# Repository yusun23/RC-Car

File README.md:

# RC-Car
Schematics for the PCB, CAD files for the Chassis and Frame Design. Along with the Code for the Embedded Systems and the materials needed to accomplish this.

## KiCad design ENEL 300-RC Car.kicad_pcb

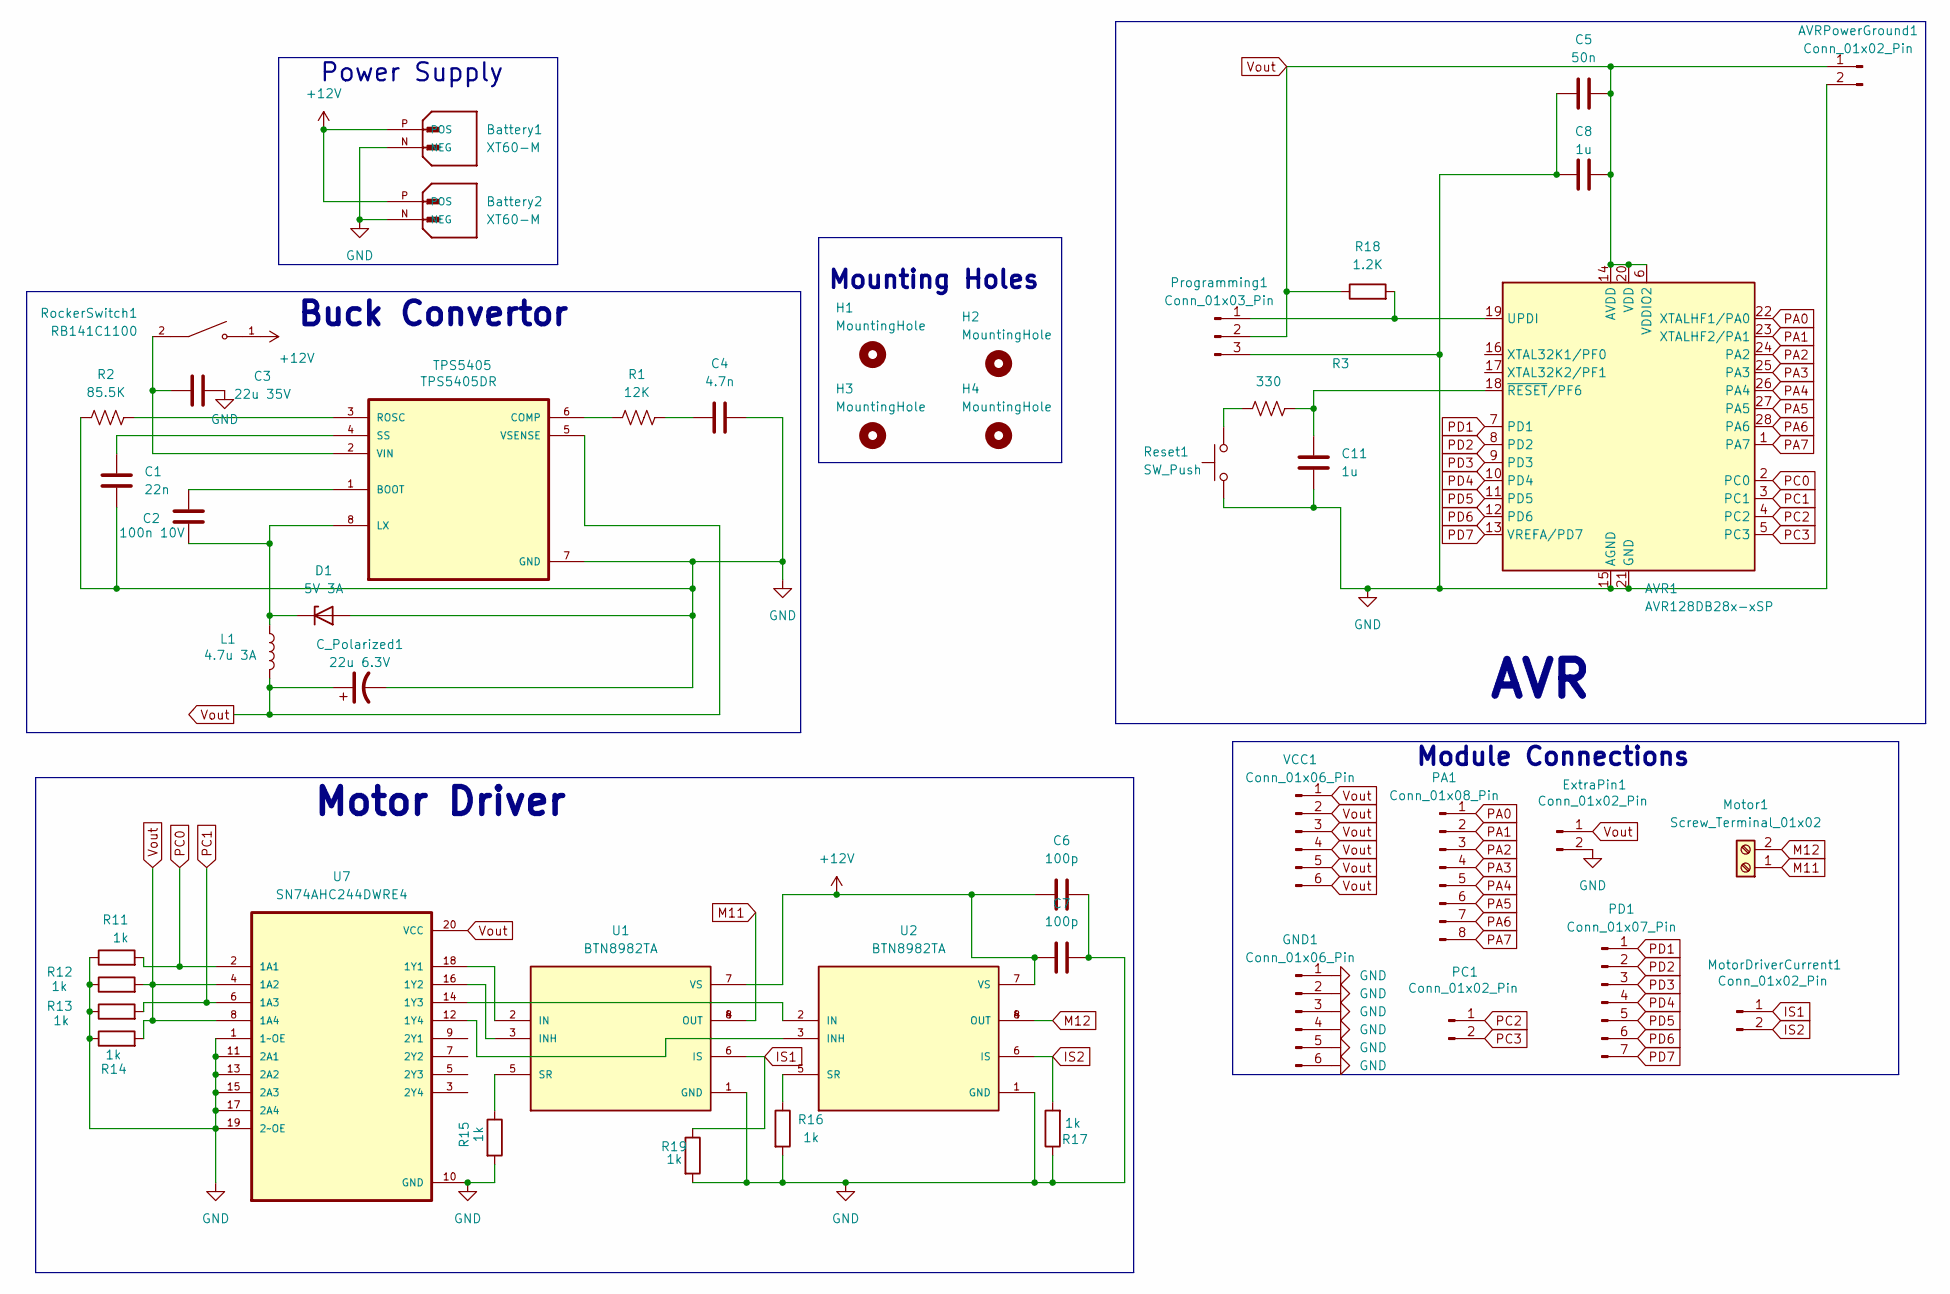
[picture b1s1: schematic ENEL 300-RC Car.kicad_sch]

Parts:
AVR1: AVR128DB28x-xSP; DIP-28_W7.62mm
AVRPowerGround1: Conn_01x02_Pin; PinHeader_1x02_P2.54mm_Vertical
Battery1, Battery2: XT60-M; AMASS_XT60-M; PARTREV V1.2
C1: 22n; C_Disc_D4.7mm_W2.5mm_P5.00mm
C2: 100n 10V; C_Radial_D4.0mm_H7.0mm_P1.50mm
C3: 22u 35V; C_Radial_D4.0mm_H7.0mm_P1.50mm
C4: 4.7n; C_Disc_D4.7mm_W2.5mm_P5.00mm
C5: 50n; C_Disc_D4.7mm_W2.5mm_P5.00mm
C6, C7: 100p; C_Disc_D4.7mm_W2.5mm_P5.00mm
C8, C11: 1u; C_Radial_D5.0mm_H11.0mm_P2.00mm
C_Polarized1: 22u 6.3V; CP_Radial_D5.0mm_P2.50mm
D1: 5V 3A; D_DO-41_SOD81_P7.62mm_Horizontal
ExtraPin1: Conn_01x02_Pin; PinHeader_1x02_P2.54mm_Vertical
GND1: Conn_01x06_Pin; PinHeader_1x06_P2.54mm_Vertical
H1, H2, H3, H4: MountingHole; MountingHole_3.2mm_M3
L1: 4.7u 3A; L_Radial_D7.0mm_P3.00mm
Motor1: Screw_Terminal_01x02; TerminalBlock_MetzConnect_Type701_RT11L02HGLU_1x02_P6.35mm_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
MotorDriverCurrent1: Conn_01x02_Pin; PinHeader_1x02_P2.54mm_Vertical
PA1: Conn_01x08_Pin; PinHeader_1x08_P2.54mm_Vertical
PC1: Conn_01x02_Pin; PinHeader_1x02_P2.54mm_Vertical
PD1: Conn_01x07_Pin; PinHeader_1x07_P2.54mm_Vertical
Programming1: Conn_01x03_Pin; PinHeader_1x03_P2.54mm_Vertical
R1: 12K; R_Axial_DIN0204_L3.6mm_D1.6mm_P5.08mm_Horizontal
R2: 85.5K; R_Axial_DIN0204_L3.6mm_D1.6mm_P5.08mm_Horizontal
R3: 330; R_Axial_DIN0204_L3.6mm_D1.6mm_P5.08mm_Horizontal
R11, R12, R13, R14, R15, R16, R17, R19: 1k; R_Axial_DIN0204_L3.6mm_D1.6mm_P5.08mm_Horizontal
R18: 1.2K; R_Axial_DIN0204_L3.6mm_D1.6mm_P5.08mm_Horizontal
Reset1: SW_Push; SW_PUSH_6mm
RockerSwitch1: RB141C1100; SW_RB141C1100; PARTREV C
TPS5405: TPS5405DR; SOIC127P599X175-8N
U1, U2: BTN8982TA; DPAK127P1500X440-8N; PARTREV 1.0
U7: SN74AHC244DWRE4; SOIC127P1030X265-20N
VCC1: Conn_01x06_Pin; PinHeader_1x06_P2.54mm_Vertical

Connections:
+12V: Battery1.P (POS), Battery2.P (POS), C6.1, C7.1, RockerSwitch1.1, U1.7 (VS), U2.7 (VS)
GND: AVR1.15 (AGND), AVR1.21 (GND), AVRPowerGround1.2, Battery1.N (NEG), Battery2.N (NEG), C1.2, C3.2, C4.2, C5.1, C6.2, C7.2, C8.1, C11.2, C_Polarized1.2, D1.2 (A), ExtraPin1.2, GND1.1, GND1.2, GND1.3, GND1.4, GND1.5, GND1.6, Programming1.3, R2.1, R11.1, R12.1, R13.1, R14.1, R15.2, R16.2, R17.1, R19.2, Reset1.1, TPS5405.7 (GND), U1.1 (GND), U2.1 (GND), U7.1 (1~OE), U7.10 (GND), U7.11 (2A1), U7.13 (2A2), U7.15 (2A3), U7.17 (2A4), U7.19 (2~OE)
IS1: MotorDriverCurrent1.1, R19.1, U1.6 (IS)
IS2: MotorDriverCurrent1.2, R17.2, U2.6 (IS)
M11: Motor1.1, U1.4 (OUT), U1.8 (OUT)
M12: Motor1.2, U2.4 (OUT), U2.8 (OUT)
unnamed: AVR1.19 (UPDI), Programming1.1, R18.2
unnamed: AVR1.18 (~RESET/PF6), C11.1, R3.2
unnamed: C4.1, R1.2
unnamed: C2.2, D1.1 (K), L1.1, TPS5405.8 (LX)
unnamed: R3.1, Reset1.2
unnamed: C2.1, TPS5405.1 (BOOT)
unnamed: R1.1, TPS5405.6 (COMP)
unnamed: R2.2, TPS5405.3 (ROSC)
unnamed: C1.1, TPS5405.4 (SS)
unnamed: C3.1, RockerSwitch1.2, TPS5405.2 (VIN)
unnamed: U1.2 (IN), U7.18 (1Y1)
unnamed: U1.3 (INH), U7.16 (1Y2)
unnamed: R15.1, U1.5 (SR)
unnamed: U2.2 (IN), U7.14 (1Y3)
unnamed: U2.3 (INH), U7.12 (1Y4)
unnamed: R16.1, U2.5 (SR)
PA0: AVR1.22 (XTALHF1/PA0), PA1.1
PA1: AVR1.23 (XTALHF2/PA1), PA1.2
PA2: AVR1.24 (PA2), PA1.3
PA3: AVR1.25 (PA3), PA1.4
PA4: AVR1.26 (PA4), PA1.5
PA5: AVR1.27 (PA5), PA1.6
PA6: AVR1.28 (PA6), PA1.7
PA7: AVR1.1 (PA7), PA1.8
PC0: AVR1.2 (PC0), R11.2, U7.2 (1A1)
PC1: AVR1.3 (PC1), R13.2, U7.6 (1A3)
PC2: AVR1.4 (PC2), PC1.1
PC3: AVR1.5 (PC3), PC1.2
PD1: AVR1.7 (PD1), PD1.1
PD2: AVR1.8 (PD2), PD1.2
PD3: AVR1.9 (PD3), PD1.3
PD4: AVR1.10 (PD4), PD1.4
PD5: AVR1.11 (PD5), PD1.5
PD6: AVR1.12 (PD6), PD1.6
PD7: AVR1.13 (VREFA/PD7), PD1.7
Vout: AVR1.6 (VDDIO2), AVR1.14 (AVDD), AVR1.20 (VDD), AVRPowerGround1.1, C5.2, C8.2, C_Polarized1.1, ExtraPin1.1, L1.2, Programming1.2, R12.2, R14.2, R18.1, TPS5405.5 (VSENSE), U7.4 (1A2), U7.8 (1A4), U7.20 (VCC), VCC1.1, VCC1.2, VCC1.3, VCC1.4, VCC1.5, VCC1.6

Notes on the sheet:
AVR
Mounting Holes
Motor Driver
Module Connections
Buck Convertor
Power Supply

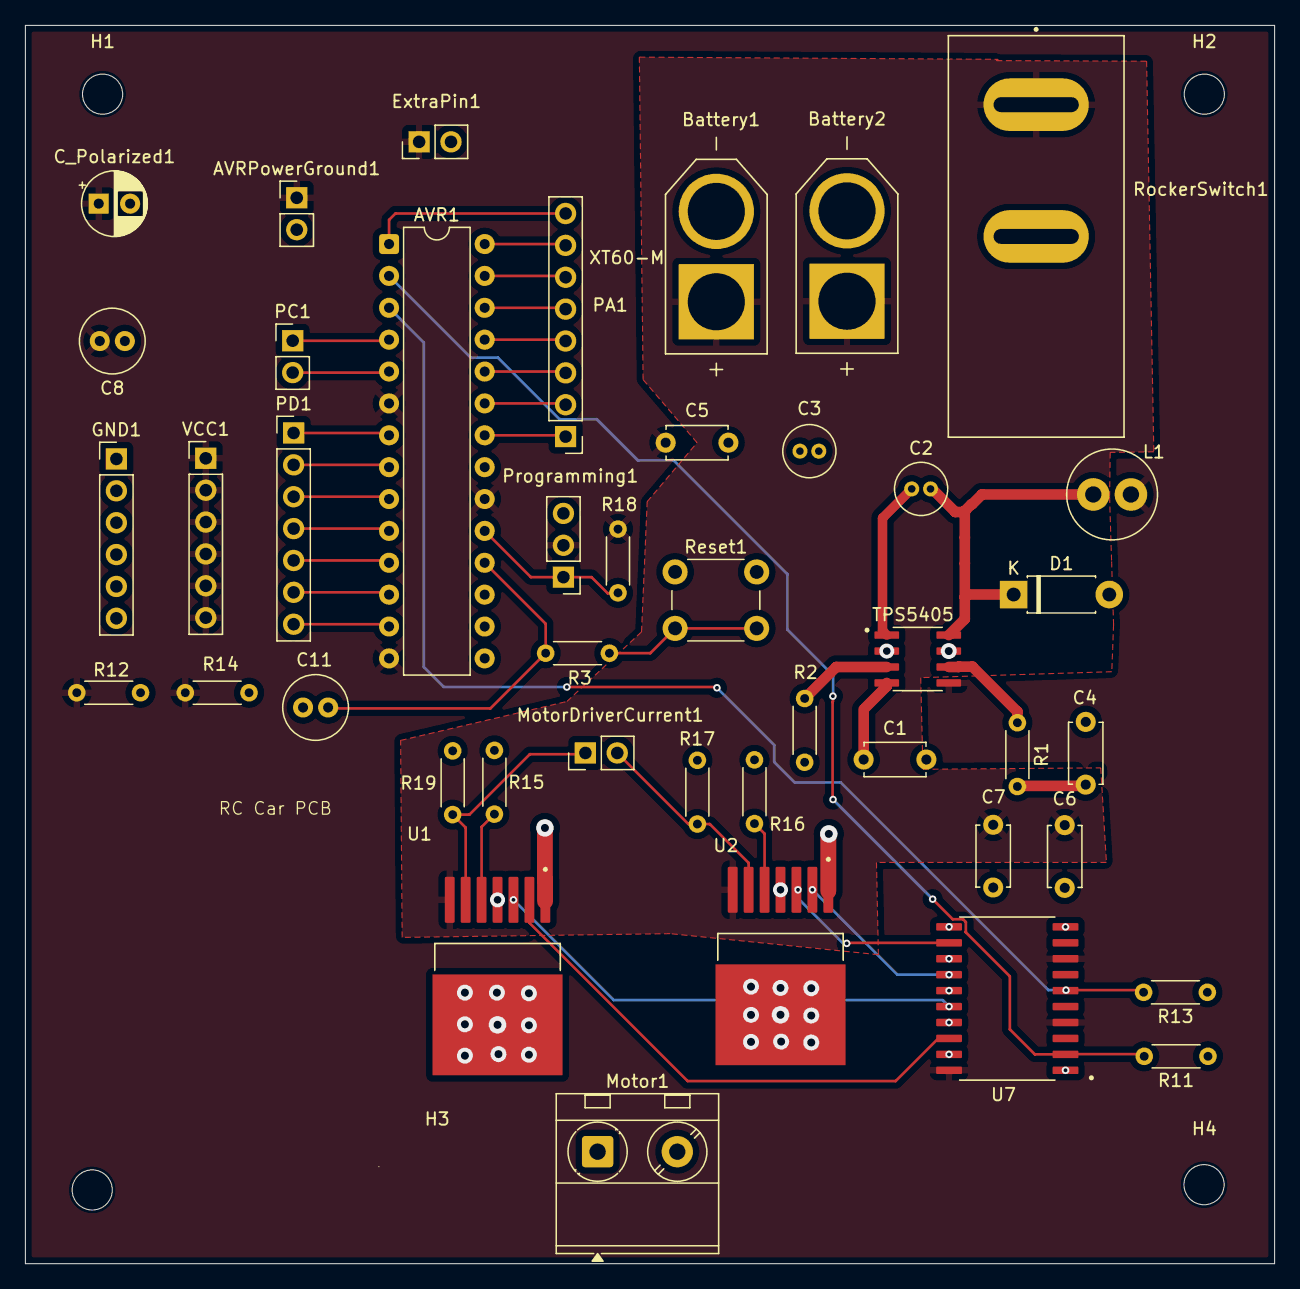
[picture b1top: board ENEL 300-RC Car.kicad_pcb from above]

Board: 2 copper layers, 99.5 x 98.7 mm, 47 parts (1 on the bottom side), 42 nets.

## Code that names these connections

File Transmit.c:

#include <avr/io.h>
#include <util/delay.h>

#define F_CPU 16000000UL

void USART0_Init(void) {
    USART0.BAUD = 6666;  // Approx. 9600 baud
    USART0.CTRLC = USART_CMODE_ASYNCHRONOUS_gc |
                   USART_PMODE_DISABLED_gc |
                   USART_CHSIZE_8BIT_gc;
    PORTA.DIRSET = PIN0_bm;  // TX
    PORTA.DIRCLR = PIN1_bm;  // RX
    USART0.CTRLB = USART_TXEN_bm | USART_RXEN_bm;
}

void USART0_Transmit(uint8_t data) {
    while (!(USART0.STATUS & USART_DREIF_bm));
    USART0.TXDATAL = data;
}

void init_io(void) {
    // Buttons on PA6, PA7
    PORTA.DIRCLR = 0b11000000;
    
    // Joystick on PD1 (Y) and PD2 (X)
    PORTD.DIRCLR = PIN1_bm | PIN2_bm;
}

void ADC0_Init(void) {
    VREF.ADC0REF = 0b10000101;      // VDD reference
    ADC0.CTRLC = 0x0C;              // Prescaler to ~125kHz
    ADC0.CTRLA = 0b00000101;        // 10-bit mode, enable
    ADC0.INTCTRL = 0x01;           // Enable result ready flag
    ADC0.COMMAND = 0x01;           // Start initial conversion
}

uint16_t ADC0_Read(uint8_t channel) {
    ADC0.MUXPOS = channel;
    
    ADC0.COMMAND = 0x01;                  // Start conversion
    while (!(ADC0.INTFLAGS & 0x01));      // Wait until done
    ADC0.INTFLAGS = 0x01;                 // Clear flag
    
    return ADC0.RES;
}

int main(void) {
    CCP = 0xD8;
    CLKCTRL.OSCHFCTRLA = 0b00011100;     // 16 MHz
    while (CLKCTRL.MCLKSTATUS & 0x01);   // Wait for sync

    USART0_Init();
    init_io();
    ADC0_Init();

    uint8_t last_l_button_state = 1, l_state = 0;
    uint8_t last_t_button_state = 1, t_state = 0;
    uint8_t light = '0', turbo = '0';
    uint8_t old_light = '0', old_turbo = '0';
    uint8_t speed = 0, turn = 0;
    uint8_t old_speed = 0, old_turn = 0;

    while (1) {
        // Light button on PA7
        uint8_t current_l_button_state = (PORTA.IN & PIN7_bm);
        if (!current_l_button_state && last_l_button_state) {
            l_state ^= 1;
            light = l_state ? '1' : '0';
        }
        last_l_button_state = current_l_button_state;

        // Turbo button on PA6
        uint8_t current_t_button_state = (PORTA.IN & PIN6_bm);
        if (!current_t_button_state && last_t_button_state) {
            t_state ^= 1;
            turbo = t_state ? '1' : '0';
        }
        last_t_button_state = current_t_button_state;

        // Read joystick Y (speed) from PD1 (AIN1)
        speed = ADC0_Read(0x01) >> 3;
        if (speed >= 60 && speed <= 68)
            speed = 64;

        // Read joystick X (turn) from PD2 (AIN2)
        turn = ADC0_Read(0x02) >> 3;
        if (turn >= 60 && turn <= 68)
            turn = 64;

        // Transmit only if something changed
        if (light != old_light || turbo != old_turbo || speed != old_speed || turn != old_turn) {
            USART0_Transmit(light);
            USART0_Transmit(turbo);
            USART0_Transmit(speed);
            USART0_Transmit(turn);
            USART0_Transmit(0x00);

            old_light = light;
            old_turbo = turbo;
            old_speed = speed;
            old_turn = turn;
        }

        _delay_ms(10);  // Optional debounce / pacing
    }
}

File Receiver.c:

/*
 * File:   Receiver.c
 * Author: yuxia
 *
 * Created on June 28, 2025, 5:19 PM
 */

#include <avr/io.h>
#include <avr/interrupt.h>
#include <stdlib.h>

#define F_CPU 16000000UL

#define RX_BUFFER_SIZE 4
volatile uint8_t rx_buffer[RX_BUFFER_SIZE];
volatile uint8_t rx_index = 0;
volatile uint8_t packet_ready = 0;
volatile uint16_t servo_pulse = 1500;  // In microseconds (default center)
volatile uint8_t pulse_phase = 0;      // 0 = HIGH phase, 1 = LOW phase
volatile uint16_t CCMP_On = 0;
volatile uint16_t CCMP_Off = 0;

/* --------- USART0 Init (only 1 line fixed) --------- */
void USART_Init(void) {
    USART0.BAUD = 6666;  // 9600 baud at 16MHz
    USART0.CTRLC = USART_CMODE_ASYNCHRONOUS_gc |
                   USART_PMODE_DISABLED_gc |
                   USART_CHSIZE_8BIT_gc;

    PORTA.DIRSET = PIN0_bm;  // TX (output)
    PORTA.DIRCLR = PIN1_bm;  // RX (input)

    USART0.CTRLB = USART_RXEN_bm;      // Enable receiver
    USART0.CTRLA = USART_RXCIE_bm;     // Enable RX Complete interrupt

    sei();  // Enable global interrupts
}
/*----------------PWM (Servo)----------------*/
void servo_Init(void){
    TCB1.CCMP = 20000;                         // Sets frequency to 50 Hz
    TCB1.CTRLA = 0b00000101;                   // Sets clock ticks to TCA0 and enables peripheral
    TCB1.CTRLB = TCB_CNTMODE_INT_gc;           // Periodic Interrupt is selected
    TCB1.INTCTRL = TCB_CAPT_bm;                // Interrupt is enabled
    sei();
}

/*-------Servo Calculations for Bit_Banging------*/
void servo_Calculations(uint8_t timing){
    double pulse = (double)timing;
    CCMP_On = (1.5+(64.0-pulse)/64.0)*1000.0;
    CCMP_Off = (18.5-((64.0-pulse)/64.0))*1000.0;
}

/* -------------USART RX Complete ISR------------- */
ISR(USART0_RXC_vect) {
    int8_t c = USART0.RXDATAL;
    if (c == 0x00) {
        rx_index = 0; // reset to start of buffer
        packet_ready = 1;
    } 
    else if (rx_index < RX_BUFFER_SIZE) {
        rx_buffer[rx_index++] = c;
    }
}

ISR(TCB1_INT_vect) {
    if (pulse_phase == 0) {
        // Start of pulse: set PA2 HIGH
        PORTA.OUT |= 0b00000100;
        if (CCMP_On < TCB1.CNT)
            TCB1.CNT = 0;         // Reset counter if CCMP is behind CNT
        TCB1.CCMP = CCMP_On;
        pulse_phase = 1;
    } else {
        PORTA.OUT &= 0b11111011;
        if (CCMP_Off < TCB1.CNT)
            TCB1.CNT = 0;         // Reset counter if CCMP is behind CNT
        TCB1.CCMP = CCMP_Off;
        TCB1.CNT = 0;          // Resets Count
        pulse_phase = 0;
    }
    // Clear interrupt flag
    TCB1.INTFLAGS = TCB_CAPT_bm;  // Clear interrupt
}


/* ----------------------   MAIN   ---------------------- */
int main(void) {
    /* === Clock === */
    CCP = 0xD8;
    CLKCTRL.OSCHFCTRLA = 0b00011100;                 // 8 MHz
    while (CLKCTRL.MCLKSTATUS & 0x01);               // Makes sure clock is ready 
    // Enable USART
    USART_Init();     // sets up USART + interrupt
    servo_Init();     // Sets up TCB1
    
    /* === PWM Setup (unchanged) === */
    PORTMUX.TCAROUTEA = 0x02;                  // Change to PORTC
    TCA0.SINGLE.CTRLA = 0b00001001;            // 16 MHz/16
    TCA0.SINGLE.CTRLB = 0x03 | (1<<4) | (1<<5);    // Normal Mode and enable CMP0, CMP1
    TCA0.SINGLE.PER   = 31;                   // Sets frequency to 16kHz
    TCA0.SINGLE.CMP0  = 0;                     // CMP0 for forward
    TCA0.SINGLE.CMP1  = 0;                     // CMP1 for backward
    
    /* === I/O Config (unchanged) === */
    PORTC.DIRSET = 0b00000011;                 // Sets PC0, PC1 as output
    PORTA.DIRSET = 0b10000100;                 // PA7 and PA2 as outputs

   /*Storage Variables*/
    uint8_t speed = 0, turning = 0, lights = 0, turbo = 0;

    while (1) {
        if (packet_ready) {
            packet_ready = 0;
            lights = rx_buffer[0];
            turbo = rx_buffer[1];
            speed = rx_buffer[2];
            turning = rx_buffer[3];
            
            // Wiggle Room for speed and turning, stopping and centering
            if (turning   < 30)
                turning = 30;
            else if (turning > 98) 
                turning = 98;
        }
        // Establishes speed and outputs as pwm
        int top_speed = 0;
        if (turbo == '1')
            top_speed = 25;
        else if (turbo == '0')
            top_speed = 20;
        int16_t signed_speed = speed - 64;
        int16_t duty = abs(signed_speed) * top_speed / 64;
        if (duty > top_speed) 
            duty = top_speed;
        else if (duty < 0)
            duty = 0;
        // Sets PWM for motor
        if (signed_speed < 0) {
            TCA0.SINGLE.CMP0 = duty;
            TCA0.SINGLE.CMP1 = 0;
        } else if (signed_speed > 0) {
            TCA0.SINGLE.CMP0 = 0;
            TCA0.SINGLE.CMP1 = duty;
        } else {
            TCA0.SINGLE.CMP0 = 0;
            TCA0.SINGLE.CMP1 = 0;
        }
        // Safeties to keep servo within range
        if (turning > 128)
            turning = 128;
        // Calculates Servo numbers
        servo_Calculations(turning);
        
        if(lights == '1')
            PORTA.OUT |= 0b10000000;
        else if (lights == '0')
            PORTA.OUT &= 0b01111111;
    }
    return 0;
}
